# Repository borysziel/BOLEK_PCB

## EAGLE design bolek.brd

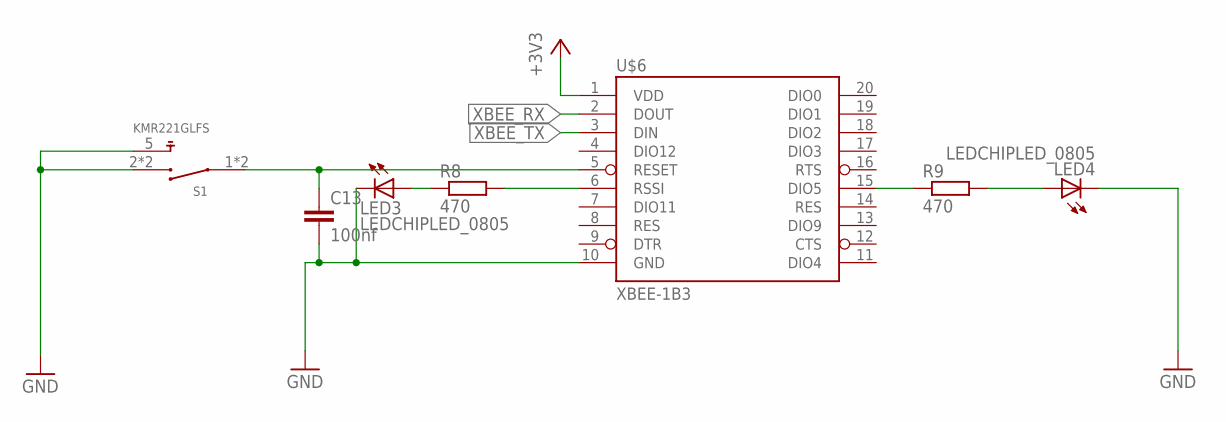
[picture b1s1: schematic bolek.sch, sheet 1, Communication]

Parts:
C13: 100nf; C0603
LED3, LED4: LEDCHIPLED_0805; CHIPLED_0805
R8, R9: 470; R0603
S1: KMR221GLFS; SW_KMR221GLFS
U$6: XBEE-1B3; XBEE-SMD

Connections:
+3V3: U$6.1 (VDD); also elsewhere on the board
GND: C13.2, LED3.C, LED4.C, S1.2 (3), S1.3, S1.5, U$6.10 (GND); also elsewhere on the board
unnamed: C13.1, S1.1, S1.4 (1), U$6.5 (RESET)
unnamed: R8.2, U$6.6 (RSSI)
unnamed: LED3.A, R8.1
unnamed: R9.1, U$6.15 (DIO5)
unnamed: LED4.A, R9.2
XBEE_RX: U$6.2 (DOUT); also elsewhere on the board
XBEE_TX: U$6.3 (DIN); also elsewhere on the board

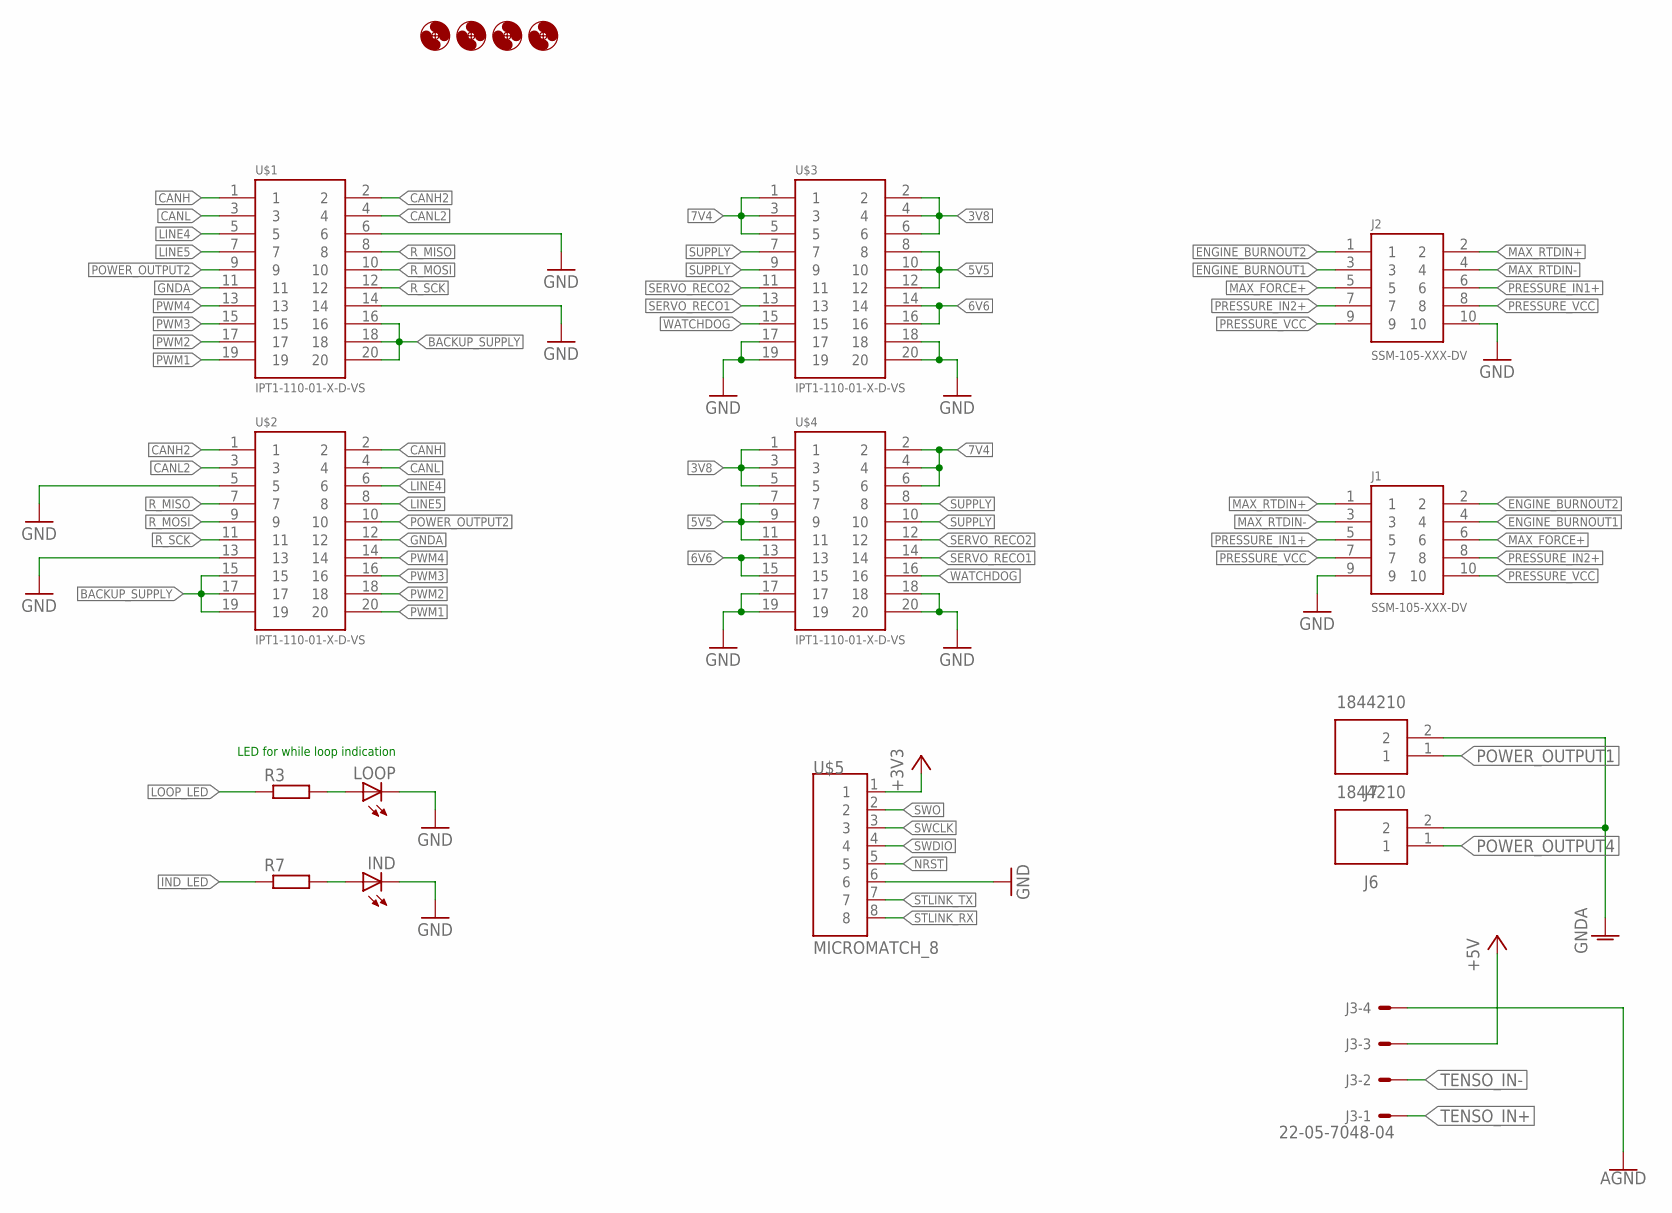
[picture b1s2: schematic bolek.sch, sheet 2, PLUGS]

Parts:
H1, H2, H3, H4: MOUNT-HOLE3.2; 3,2
IND: LEDCHIPLED_0603; CHIPLED_0603
J1, J2: SSM-105-XXX-DV
J3: 22-05-7048-04; 7395-04
J6, J7: 1844210; SHDR2W100P0X350_1X2_840X920X72
LOOP: LEDCHIPLED_0603; CHIPLED_0603
R3, R7: R-EU_R0603; R0603
U$1, U$2, U$3, U$4: IPT1-110-01-X-D-VS
U$5: MICROMATCH_8

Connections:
3V8: U$3.2, U$3.4, U$3.6, U$4.1, U$4.3, U$4.5; also elsewhere on the board
5V5: U$3.8, U$3.10, U$3.12, U$4.7, U$4.9, U$4.11; also elsewhere on the board
6V6: U$3.14, U$3.16, U$4.13, U$4.15
7V4: U$3.1, U$3.3, U$3.5, U$4.2, U$4.4, U$4.6
+3V3: U$5.1; also elsewhere on the board
+5V: J3.3; also elsewhere on the board
AGND: J3.4; also elsewhere on the board
BACKUP_SUPPLY: U$1.16, U$1.18, U$1.20, U$2.15, U$2.17, U$2.19
CANH: U$1.1, U$2.2; also elsewhere on the board
CANH2: U$1.2, U$2.1; also elsewhere on the board
CANL: U$1.3, U$2.4; also elsewhere on the board
CANL2: U$1.4, U$2.3; also elsewhere on the board
ENGINE_BURNOUT1: J1.4, J2.3; also elsewhere on the board
ENGINE_BURNOUT2: J1.2, J2.1; also elsewhere on the board
GND: IND.C, J1.9, J2.10, LOOP.C, U$1.6, U$1.14, U$2.5, U$2.13, U$3.17, U$3.18, U$3.19, U$3.20, U$4.17, U$4.18, U$4.19, U$4.20, U$5.6; also elsewhere on the board
GNDA: J6.2, J7.2, U$1.11, U$2.12; also elsewhere on the board
IND_LED: R7.1; also elsewhere on the board
LINE4: U$1.5, U$2.6
LINE5: U$1.7, U$2.8
LOOP_LED: R3.1; also elsewhere on the board
MAX_FORCE+: J1.6, J2.5; also elsewhere on the board
MAX_RTDIN+: J1.1, J2.2; also elsewhere on the board
MAX_RTDIN-: J1.3, J2.4; also elsewhere on the board
unnamed: LOOP.A, R3.2
unnamed: IND.A, R7.2
NRST: U$5.5; also elsewhere on the board
POWER_OUTPUT1: J7.1; also elsewhere on the board
POWER_OUTPUT2: U$1.9, U$2.10; also elsewhere on the board
POWER_OUTPUT4: J6.1; also elsewhere on the board
PRESSURE_IN1+: J1.5, J2.6; also elsewhere on the board
PRESSURE_IN2+: J1.8, J2.7; also elsewhere on the board
PRESSURE_VCC: J1.7, J1.10, J2.8, J2.9; also elsewhere on the board
PWM1: U$1.19, U$2.20; also elsewhere on the board
PWM2: U$1.17, U$2.18; also elsewhere on the board
PWM3: U$1.15, U$2.16
PWM4: U$1.13, U$2.14
R_MISO: U$1.8, U$2.7
R_MOSI: U$1.10, U$2.9
R_SCK: U$1.12, U$2.11
SERVO_RECO1: U$3.13, U$4.14
SERVO_RECO2: U$3.11, U$4.12
STLINK_RX: U$5.8; also elsewhere on the board
STLINK_TX: U$5.7; also elsewhere on the board
SUPPLY: U$3.7, U$3.9, U$4.8, U$4.10; also elsewhere on the board
SWCLK: U$5.3; also elsewhere on the board
SWDIO: U$5.4; also elsewhere on the board
SWO: U$5.2
TENSO_IN+: J3.1; also elsewhere on the board
TENSO_IN-: J3.2; also elsewhere on the board
WATCHDOG: U$3.15, U$4.16

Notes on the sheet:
LED for while loop indication

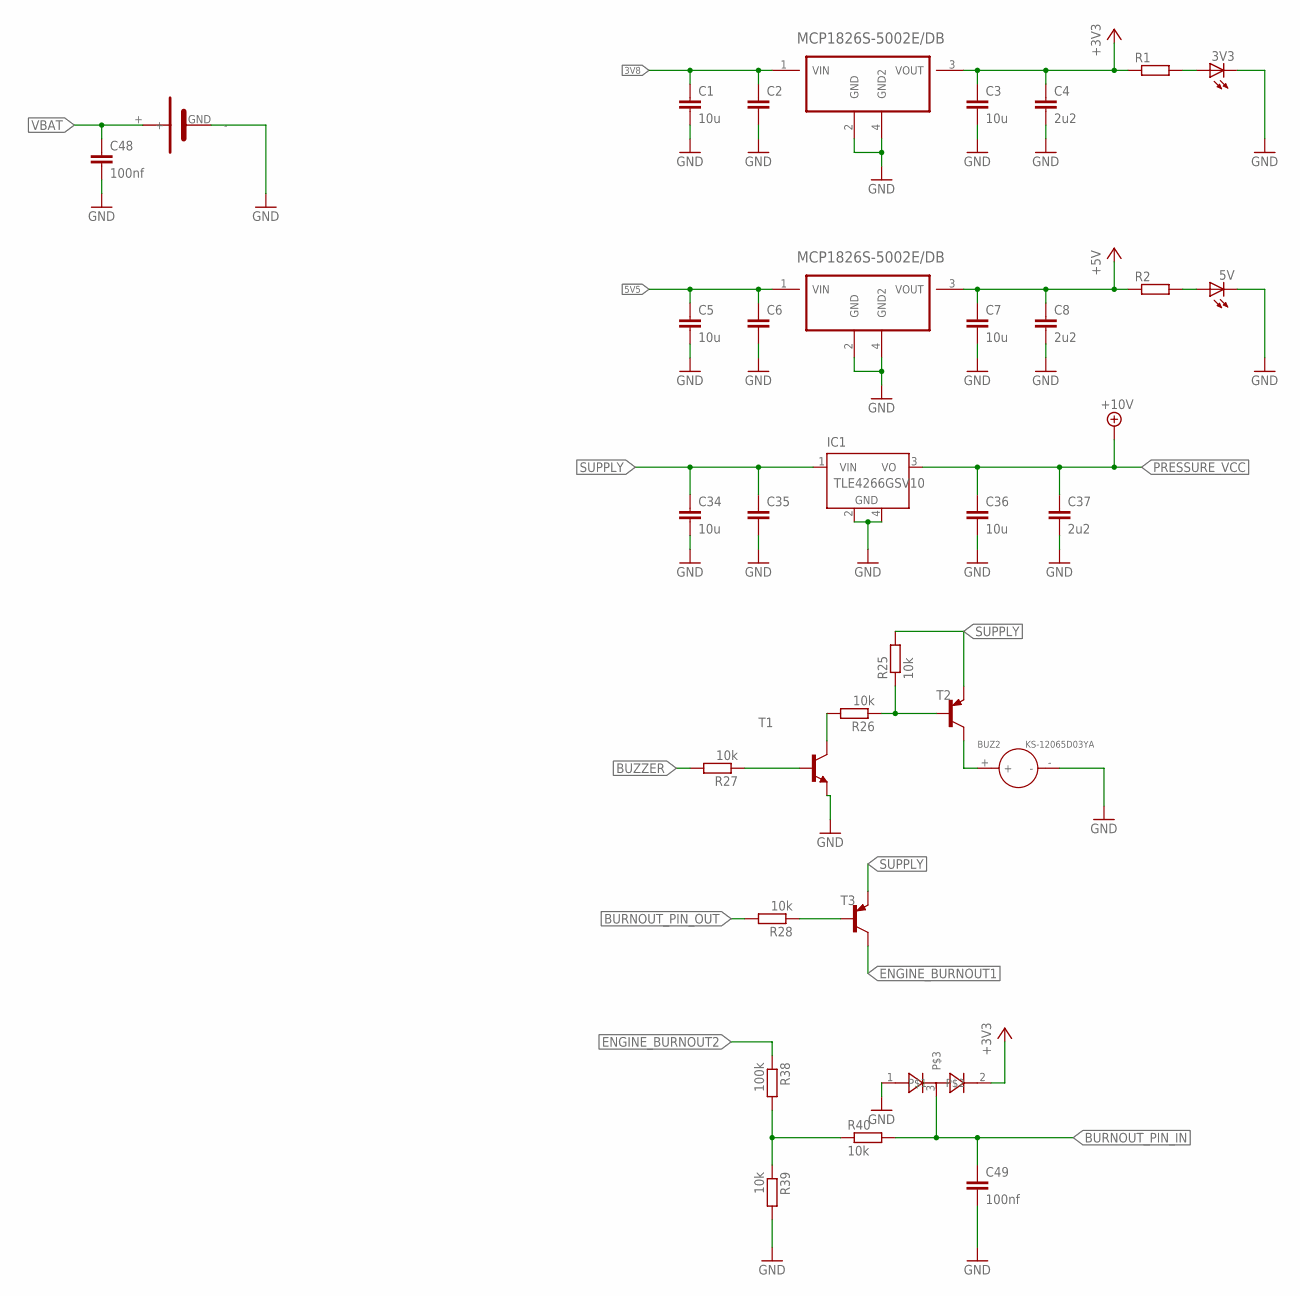
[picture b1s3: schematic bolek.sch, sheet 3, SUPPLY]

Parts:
3V3, 5V: LEDCHIPLED_0603; CHIPLED_0603
BUZ2: KS-12065D03YA; BZ2-7.6-D12.0XH6.5MM
C1, C3, C5, C7, C34, C36: 10u; C0805K
C2, C6, C35: C-EUC0805K; C0805K
C4, C8, C37: 2u2; C0805K
C48: 100nf; C0805K
C49: 100nf; C0603
IC1: TLE4266GSV10; SOT223
R1, R2: R-EU_R0603; R0603
R25, R26, R27, R28, R39, R40: 10k; R0603
R38: 100k; R0603
T1: BCW81-NPN-SOT23-BEC; SOT23-BEC
T2, T3: BC807-16-PNP-SOT23-BEC; SOT23-BEC
U1, U2: MCP1826S-5002E/DB; SOT230P700X180-4N
U$32: CR1220_POZ
U$40: BAS40W-04; SOT65P210X110-3N

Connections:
3V8: C1.1, C2.1, U1.1 (VIN); also elsewhere on the board
5V5: C5.1, C6.1, U2.1 (VIN); also elsewhere on the board
+3V3: C3.1, C4.1, R1.1, U1.3 (VOUT), U$40.2; also elsewhere on the board
+5V: C7.1, C8.1, R2.1, U2.3 (VOUT); also elsewhere on the board
BURNOUT_PIN_IN: C49.1, R40.2, U$40.3; also elsewhere on the board
BURNOUT_PIN_OUT: R28.2; also elsewhere on the board
BUZZER: R27.2; also elsewhere on the board
ENGINE_BURNOUT1: T3.C; also elsewhere on the board
ENGINE_BURNOUT2: R38.1; also elsewhere on the board
GND: 3V3.C, 5V.C, BUZ2.-, C1.2, C2.2, C3.2, C4.2, C5.2, C6.2, C7.2, C8.2, C34.2, C35.2, C36.2, C37.2, C48.2, C49.2, IC1.2 (GND), IC1.4 (GND), R39.2, T1.E, U1.2 (GND), U1.4 (GND2), U2.2 (GND), U2.4 (GND2), U$32.GND (-), U$40.1; also elsewhere on the board
unnamed: 3V3.A, R1.2
unnamed: 5V.A, R2.2
unnamed: R25.1, R26.1, T2.B
unnamed: BUZ2.+, T2.C
unnamed: R26.2, T1.C
unnamed: R27.1, T1.B
unnamed: R28.1, T3.B
unnamed: R38.2, R39.1, R40.1
PRESSURE_VCC: C36.1, C37.1, IC1.3 (VO); also elsewhere on the board
SUPPLY: C34.1, C35.1, IC1.1 (VIN), R25.2, T2.E, T3.E; also elsewhere on the board
VBAT: C48.1, U$32.+; also elsewhere on the board

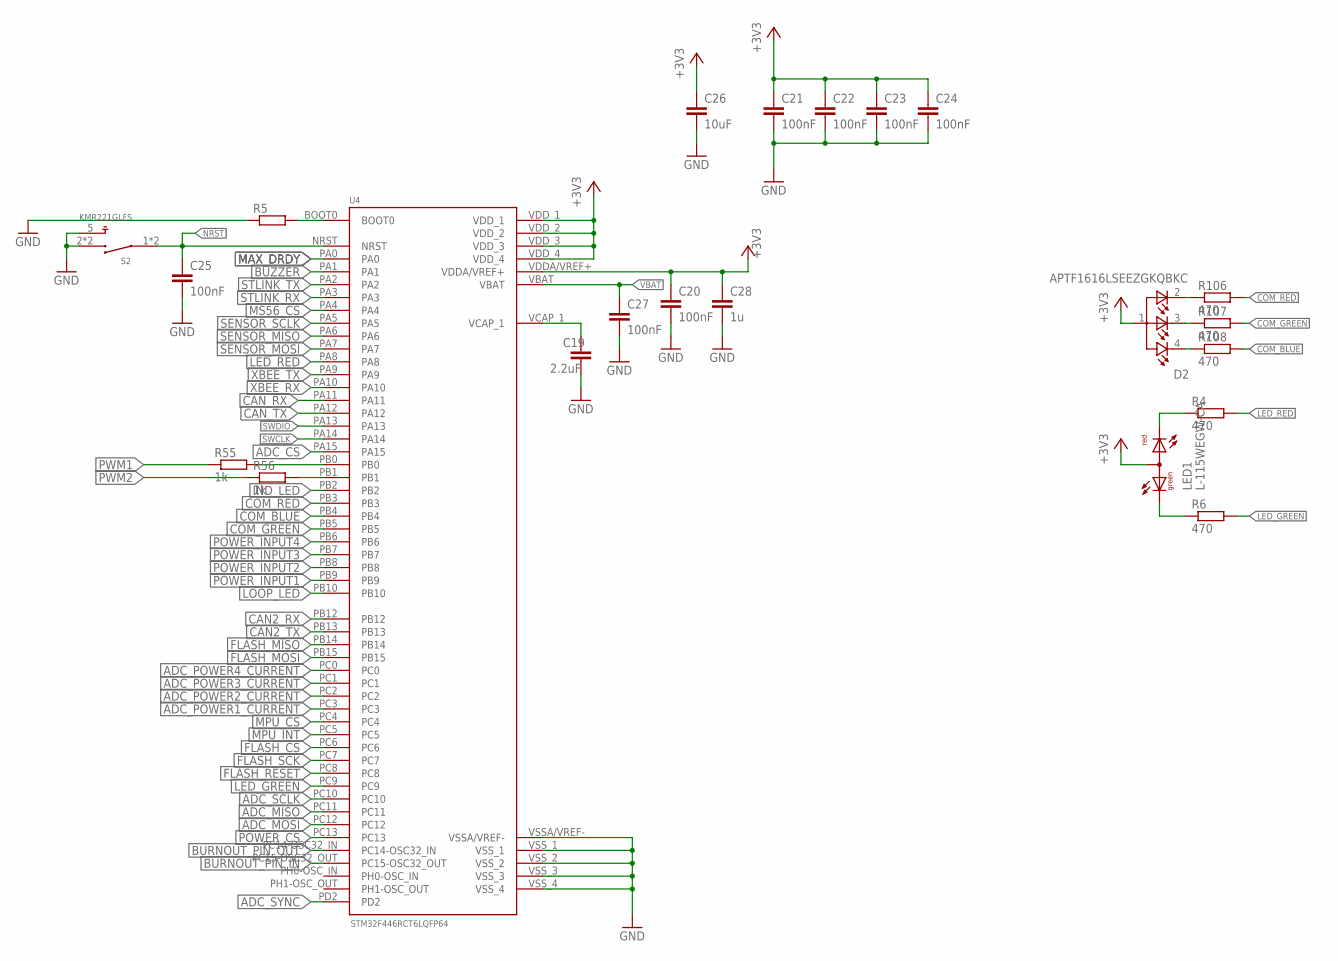
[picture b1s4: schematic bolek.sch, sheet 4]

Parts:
C19: 2.2uF; C0603K
C20, C21, C22, C23, C24, C25, C27: 100nF; C0603K
C26: 10uF; C0805K
C28: 1u; C0603K
D2: APTF1616LSEEZGKQBKC; LEDSC160X160X070-4N
LED1: L-115WEGW-CA; DUOLED-A-3MM
R4, R6, R106, R107, R108: 470; R0603
R5: R-EU_R0603; R0603
R55, R56: 1k; R0603
S2: KMR221GLFS; SW_KMR221GLFS
U4: STM32F446RCT6LQFP64; QFP50P1290X1290X120-64

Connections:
+3V3: C20.1, C21.1, C22.1, C23.1, C24.1, C26.1, C28.1, D2.1, LED1.2 (A), U4.VDDA/VREF+, U4.VDD_1, U4.VDD_2, U4.VDD_3, U4.VDD_4; also elsewhere on the board
ADC_CS: U4.PA15; also elsewhere on the board
ADC_MISO: U4.PC11; also elsewhere on the board
ADC_MOSI: U4.PC12; also elsewhere on the board
ADC_POWER1_CURRENT: U4.PC3; also elsewhere on the board
ADC_POWER2_CURRENT: U4.PC2; also elsewhere on the board
ADC_POWER3_CURRENT: U4.PC1; also elsewhere on the board
ADC_POWER4_CURRENT: U4.PC0; also elsewhere on the board
ADC_SCLK: U4.PC10; also elsewhere on the board
ADC_SYNC: U4.PD2; also elsewhere on the board
BURNOUT_PIN_IN: U4.PC15-OSC32_OUT; also elsewhere on the board
BURNOUT_PIN_OUT: U4.PC14-OSC32_IN; also elsewhere on the board
BUZZER: U4.PA1; also elsewhere on the board
CAN2_RX: U4.PB12; also elsewhere on the board
CAN2_TX: U4.PB13; also elsewhere on the board
CAN_RX: U4.PA11; also elsewhere on the board
CAN_TX: U4.PA12; also elsewhere on the board
COM_BLUE: R108.2, U4.PB4
COM_GREEN: R107.2, U4.PB5
COM_RED: R106.2, U4.PB3
FLASH_CS: U4.PC6; also elsewhere on the board
FLASH_MISO: U4.PB14; also elsewhere on the board
FLASH_MOSI: U4.PB15; also elsewhere on the board
FLASH_RESET: U4.PC8; also elsewhere on the board
FLASH_SCK: U4.PC7; also elsewhere on the board
GND: C19.2, C20.2, C21.2, C22.2, C23.2, C24.2, C25.2, C26.2, C27.2, C28.2, R5.1, S2.2 (3), S2.3, S2.5, U4.VSSA/VREF-, U4.VSS_1, U4.VSS_2, U4.VSS_3, U4.VSS_4; also elsewhere on the board
IND_LED: U4.PB2; also elsewhere on the board
LED_GREEN: R6.2, U4.PC9
LED_RED: R4.2, U4.PA8
LOOP_LED: U4.PB10; also elsewhere on the board
MAX_DRDY: U4.PA0; also elsewhere on the board
MPU_CS: U4.PC4; also elsewhere on the board
MPU_INT: U4.PC5; also elsewhere on the board
MS56_CS: U4.PA4; also elsewhere on the board
unnamed: LED1.3 (CR), R4.1
unnamed: R5.2, U4.BOOT0
unnamed: LED1.1 (CG), R6.1
unnamed: R55.2, U4.PB0
unnamed: R56.2, U4.PB1
unnamed: D2.2, R106.1
unnamed: D2.3, R107.1
unnamed: D2.4, R108.1
NRST: C25.1, S2.1, S2.4 (1), U4.NRST; also elsewhere on the board
POWER_CS: U4.PC13; also elsewhere on the board
POWER_INPUT1: U4.PB9; also elsewhere on the board
POWER_INPUT2: U4.PB8; also elsewhere on the board
POWER_INPUT3: U4.PB7; also elsewhere on the board
POWER_INPUT4: U4.PB6; also elsewhere on the board
PWM1: R55.1; also elsewhere on the board
PWM2: R56.1; also elsewhere on the board
SENSOR_MISO: U4.PA6; also elsewhere on the board
SENSOR_MOSI: U4.PA7; also elsewhere on the board
SENSOR_SCLK: U4.PA5; also elsewhere on the board
STLINK_RX: U4.PA3; also elsewhere on the board
STLINK_TX: U4.PA2; also elsewhere on the board
SWCLK: U4.PA14; also elsewhere on the board
SWDIO: U4.PA13; also elsewhere on the board
VBAT: C27.1, U4.VBAT; also elsewhere on the board
VCAP1: C19.1, U4.VCAP_1
XBEE_RX: U4.PA10; also elsewhere on the board
XBEE_TX: U4.PA9; also elsewhere on the board

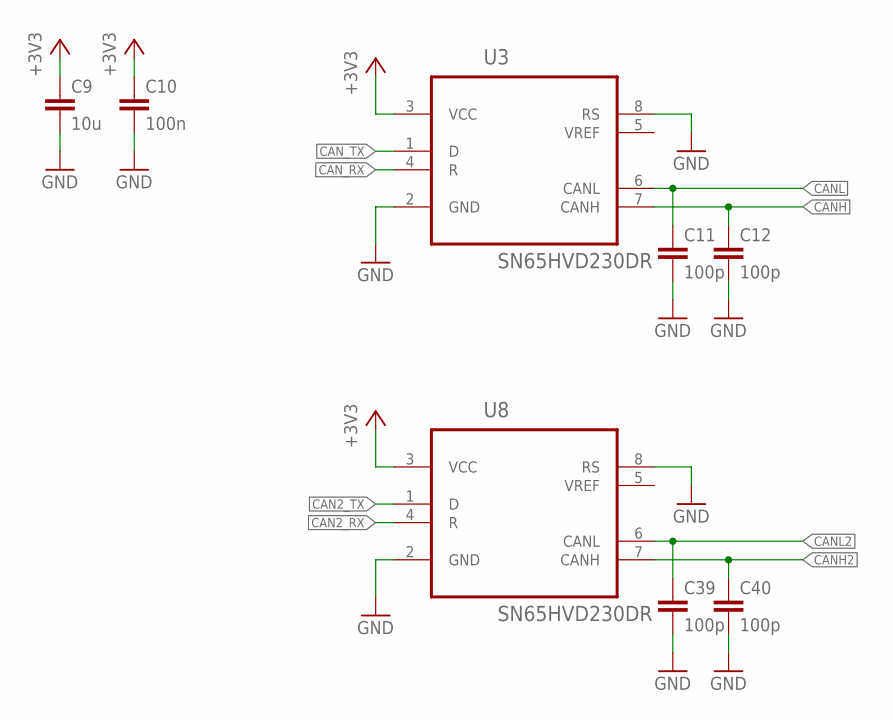
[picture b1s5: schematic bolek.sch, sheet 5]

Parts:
C9: 10u; C0805K
C10: 100n; C0603K
C11, C12, C39, C40: 100p; C0603K
U3, U8: SN65HVD230DR; SOIC127P600X175-8N

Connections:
+3V3: C9.1, C10.1, U3.3 (VCC), U8.3 (VCC); also elsewhere on the board
CAN2_RX: U8.4 (R); also elsewhere on the board
CAN2_TX: U8.1 (D); also elsewhere on the board
CANH: C12.1, U3.7 (CANH); also elsewhere on the board
CANH2: C40.1, U8.7 (CANH); also elsewhere on the board
CANL: C11.1, U3.6 (CANL); also elsewhere on the board
CANL2: C39.1, U8.6 (CANL); also elsewhere on the board
CAN_RX: U3.4 (R); also elsewhere on the board
CAN_TX: U3.1 (D); also elsewhere on the board
GND: C9.2, C10.2, C11.2, C12.2, C39.2, C40.2, U3.2 (GND), U3.8 (RS), U8.2 (GND), U8.8 (RS); also elsewhere on the board

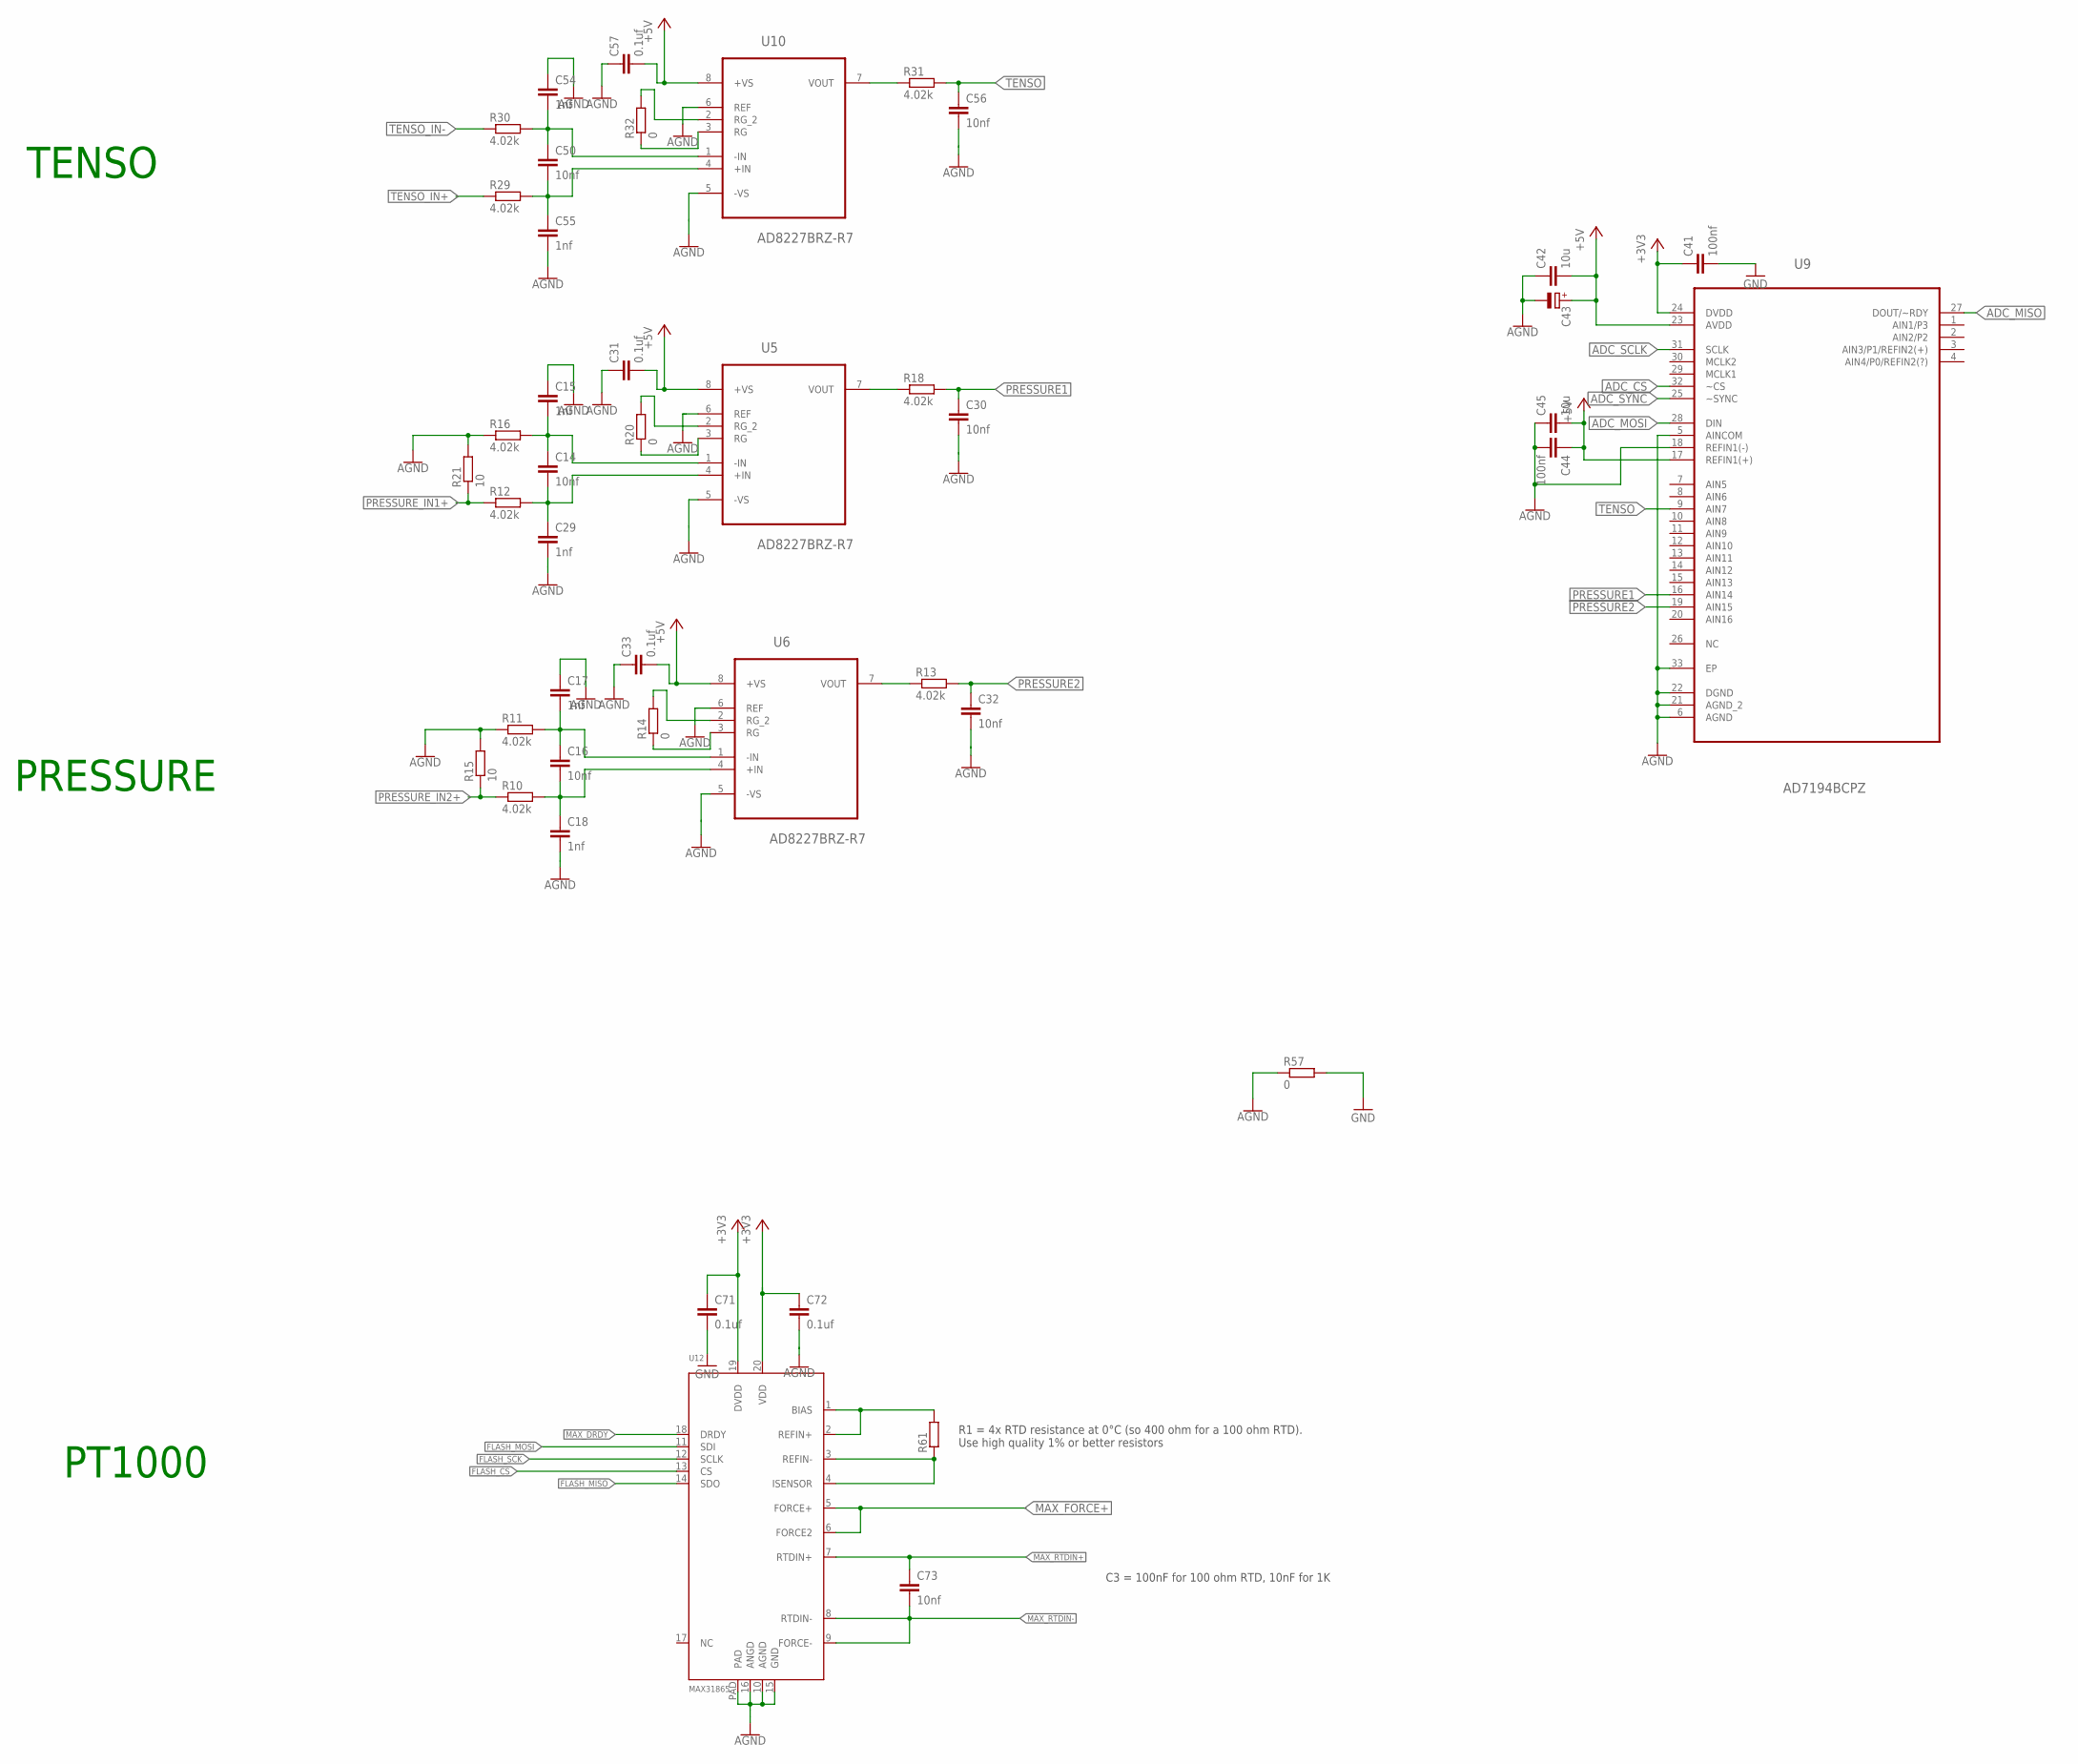
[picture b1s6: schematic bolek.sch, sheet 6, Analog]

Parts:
C14, C16, C30, C32, C50, C56, C73: 10nf; C0603
C15, C17, C18, C29, C54, C55: 1nf; C0603
C31, C33, C57, C71, C72: 0.1uf; C0603
C41, C44: 100nf; C0603K
C42, C45: 10u; C0805K
C43: CPOL-EUSMCA; SMC_A
R10, R11, R12, R13, R16, R18, R29, R30, R31: 4.02k; R0603
R14, R20, R32: 0; R0805
R15, R21: 10; R0603
R57: 0; R0603
R61: R-EU_R0805; R0805
U5, U6, U10: AD8227BRZ-R7; SOIC127P600X175-8N
U9: AD7194BCPZ; QFN50P500X500X80-33N
U12: MAX31865; QFN20_4MM_0.65MM

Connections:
+3V3: C41.1, C71.1, C72.1, U9.24 (DVDD), U12.19 (DVDD), U12.20 (VDD); also elsewhere on the board
+5V: C31.2, C33.2, C42.2, C43.+, C44.1, C45.2, C57.2, U5.8 (+VS), U6.8 (+VS), U9.17 (REFIN1(+)), U9.23 (AVDD), U10.8 (+VS); also elsewhere on the board
ADC_CS: U9.32 (~CS); also elsewhere on the board
ADC_MISO: U9.27 (DOUT/~RDY); also elsewhere on the board
ADC_MOSI: U9.28 (DIN); also elsewhere on the board
ADC_SCLK: U9.31 (SCLK); also elsewhere on the board
ADC_SYNC: U9.25 (~SYNC); also elsewhere on the board
AGND: C15.1, C17.1, C18.2, C29.2, C30.2, C31.1, C32.2, C33.1, C42.1, C43.-, C44.2, C45.1, C54.1, C55.2, C56.2, C57.1, C72.2, R11.1, R15.2, R16.1, R21.2, R57.1, U5.5 (-VS), U5.6 (REF), U6.5 (-VS), U6.6 (REF), U9.5 (AINCOM), U9.6 (AGND), U9.18 (REFIN1(-)), U9.21 (AGND_2), U9.22 (DGND), U9.33 (EP), U10.5 (-VS), U10.6 (REF), U12.10 (AGND), U12.15 (GND), U12.16 (ANGD), U12.PAD; also elsewhere on the board
FLASH_CS: U12.13 (CS); also elsewhere on the board
FLASH_MISO: U12.14 (SDO); also elsewhere on the board
FLASH_MOSI: U12.11 (SDI); also elsewhere on the board
FLASH_SCK: U12.12 (SCLK); also elsewhere on the board
GND: C41.2, C71.2, R57.2; also elsewhere on the board
MAX_DRDY: U12.18 (DRDY); also elsewhere on the board
MAX_FORCE+: U12.5 (FORCE+), U12.6 (FORCE2); also elsewhere on the board
MAX_RTDIN+: C73.1, U12.7 (RTDIN+); also elsewhere on the board
MAX_RTDIN-: C73.2, U12.8 (RTDIN-), U12.9 (FORCE-); also elsewhere on the board
unnamed: C16.1, C17.2, R11.2, U6.1 (-IN)
unnamed: C16.2, C18.1, R10.2, U6.4 (+IN)
unnamed: R13.1, U6.7 (VOUT)
unnamed: R14.1, U6.3 (RG)
unnamed: R14.2, U6.2 (RG_2)
unnamed: R61.2, U12.1 (BIAS), U12.2 (REFIN+)
unnamed: R61.1, U12.3 (REFIN-), U12.4 (ISENSOR)
unnamed: C14.1, C15.2, R16.2, U5.1 (-IN)
unnamed: C14.2, C29.1, R12.2, U5.4 (+IN)
unnamed: R18.1, U5.7 (VOUT)
unnamed: R20.1, U5.3 (RG)
unnamed: R20.2, U5.2 (RG_2)
unnamed: C50.1, C54.2, R30.2, U10.1 (-IN)
unnamed: C50.2, C55.1, R29.2, U10.4 (+IN)
unnamed: R31.1, U10.7 (VOUT)
unnamed: R32.1, U10.3 (RG)
unnamed: R32.2, U10.2 (RG_2)
PRESSURE1: C30.1, R18.2, U9.16 (AIN14)
PRESSURE2: C32.1, R13.2, U9.19 (AIN15)
PRESSURE_IN1+: R12.1, R21.1; also elsewhere on the board
PRESSURE_IN2+: R10.1, R15.1; also elsewhere on the board
TENSO: C56.1, R31.2, U9.9 (AIN7)
TENSO_IN+: R29.1; also elsewhere on the board
TENSO_IN-: R30.1; also elsewhere on the board

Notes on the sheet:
PRESSURE
TENSO
C3 = 100nF for 100 ohm RTD, 10nF for 1K
R1 = 4x RTD resistance at 0°C (so 400 ohm for a 100 ohm RTD). Use high quality 1% or better resistors
PT1000

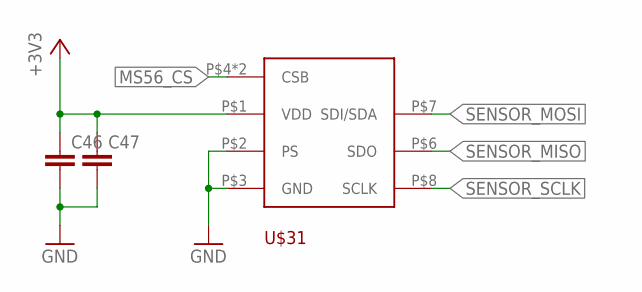
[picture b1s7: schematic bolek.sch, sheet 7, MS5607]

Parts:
C46, C47: C-EUC0603; C0603
U$31: MS56XX

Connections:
+3V3: C46.1, C47.1, U$31.P$1 (VDD); also elsewhere on the board
GND: C46.2, C47.2, U$31.P$2 (PS), U$31.P$3 (GND); also elsewhere on the board
MS56_CS: U$31.P$4 (CSB), U$31.P$5 (CSB); also elsewhere on the board
SENSOR_MISO: U$31.P$6 (SDO); also elsewhere on the board
SENSOR_MOSI: U$31.P$7 (SDI/SDA); also elsewhere on the board
SENSOR_SCLK: U$31.P$8 (SCLK); also elsewhere on the board

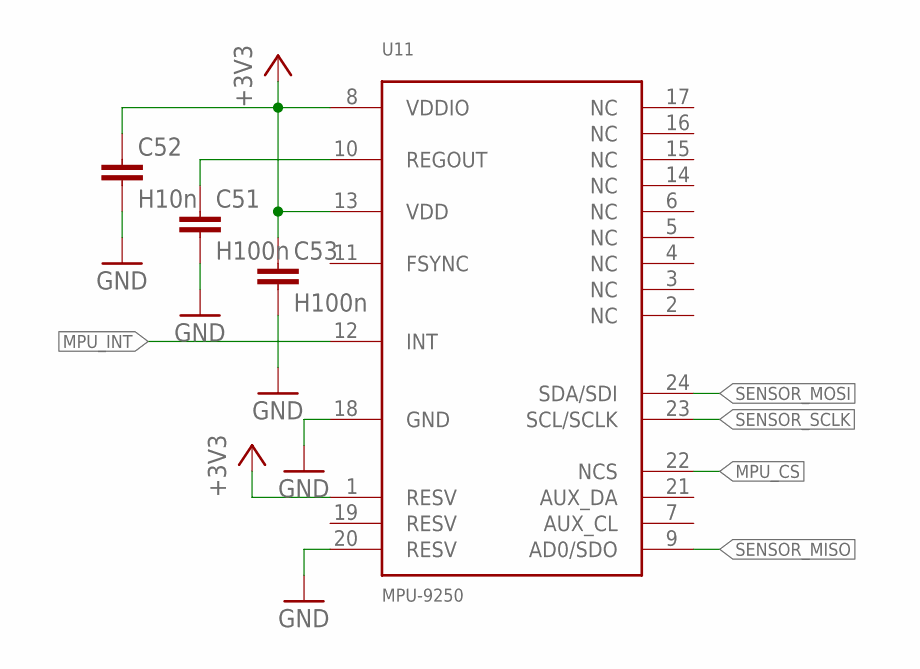
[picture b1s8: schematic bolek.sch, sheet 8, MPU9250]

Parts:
C51, C53: H100n; C0603K
C52: H10n; C0603K
U11: MPU-9250

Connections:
+3V3: C52.1, C53.1, U11.1 (RESV), U11.8 (VDDIO), U11.13 (VDD); also elsewhere on the board
GND: C51.2, C52.2, C53.2, U11.18 (GND), U11.20 (RESV); also elsewhere on the board
MPU_CS: U11.22 (NCS); also elsewhere on the board
MPU_INT: U11.12 (INT); also elsewhere on the board
unnamed: C51.1, U11.10 (REGOUT)
SENSOR_MISO: U11.9 (AD0/SDO); also elsewhere on the board
SENSOR_MOSI: U11.24 (SDA/SDI); also elsewhere on the board
SENSOR_SCLK: U11.23 (SCL/SCLK); also elsewhere on the board

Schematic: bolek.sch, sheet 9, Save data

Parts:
C58: 100nf; C0603
R33, R34, R35, R36, R37: 10; R0603
U$39: S25FLX; SOIC16

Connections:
+3V3: C58.1, U$39.2 (VCC); also elsewhere on the board
FLASH_CS: R36.2; also elsewhere on the board
FLASH_MISO: R35.2; also elsewhere on the board
FLASH_MOSI: R34.2; also elsewhere on the board
FLASH_RESET: R37.1; also elsewhere on the board
FLASH_SCK: R33.2; also elsewhere on the board
GND: C58.2, U$39.10 (VSS); also elsewhere on the board
unnamed: R33.1, U$39.16 (SCK)
unnamed: R34.1, U$39.15 (SI)
unnamed: R35.1, U$39.8 (SO)
unnamed: R36.1, U$39.7 (!CS)
unnamed: R37.2, U$39.3 (!RESET)

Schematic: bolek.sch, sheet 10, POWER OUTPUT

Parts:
C59, C60: 100nf; C0603
C61, C62, C63, C64, C65, C66, C67, C68: 10nf; C0603
D1: DIODE-SOD123; SOD123
R41, R42, R43, R44, R45, R46, R47, R48, R49: 10k; R0603
R50, R51, R52, R53, R54: 1k; R0603
R58: 0; R0603
VNQ5027AK-E1: VNQ5027AK-E; POWERSSO-24

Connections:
ADC_POWER1_CURRENT: C65.1, R46.2, R50.1; also elsewhere on the board
ADC_POWER2_CURRENT: C66.1, R47.2, R51.1; also elsewhere on the board
ADC_POWER3_CURRENT: C67.1, R48.2, R52.1; also elsewhere on the board
ADC_POWER4_CURRENT: C68.1, R49.2, R53.1; also elsewhere on the board
AGND: R58.2; also elsewhere on the board
GNDA: C59.2, C60.2, C61.2, C62.2, C63.2, C64.2, C65.2, C66.2, C67.2, C68.2, D1.C, R50.2, R51.2, R52.2, R53.2, R54.1, R58.1; also elsewhere on the board
unnamed: R46.1, VNQ5027AK-E1.P$4 (CURRENT_SENSE1)
unnamed: R47.1, VNQ5027AK-E1.P$6 (CURRENT_SENSE2)
unnamed: R48.1, VNQ5027AK-E1.P$8 (CURRENT_SENSE3)
unnamed: R49.1, VNQ5027AK-E1.P$10 (CURRENT_SENSE4)
unnamed: R41.2, VNQ5027AK-E1.P$3 (INPUT1)
unnamed: R42.2, VNQ5027AK-E1.P$5 (INPUT2)
unnamed: R43.2, VNQ5027AK-E1.P$7 (INPUT3)
unnamed: R44.2, VNQ5027AK-E1.P$9 (INPUT4)
unnamed: R45.2, VNQ5027AK-E1.P$11 (CS_DIS)
unnamed: D1.A, R54.2, VNQ5027AK-E1.P$2 (GND)
POWER_CS: R45.1; also elsewhere on the board
POWER_INPUT1: R41.1; also elsewhere on the board
POWER_INPUT2: R42.1; also elsewhere on the board
POWER_INPUT3: R43.1; also elsewhere on the board
POWER_INPUT4: R44.1; also elsewhere on the board
POWER_OUTPUT1: C61.1, VNQ5027AK-E1.P$13 (OUTPUT1_1), VNQ5027AK-E1.P$14 (OUTPUT1_2), VNQ5027AK-E1.P$15 (OUTPUT1_3); also elsewhere on the board
POWER_OUTPUT2: C62.1, VNQ5027AK-E1.P$16 (OUTPUT2_1), VNQ5027AK-E1.P$17 (OUTPUT2_2), VNQ5027AK-E1.P$18 (OUTPUT2_3); also elsewhere on the board
POWER_OUTPUT3: C63.1, VNQ5027AK-E1.P$19 (OUTPUT3_1), VNQ5027AK-E1.P$20 (OUTPUT3_2), VNQ5027AK-E1.P$21 (OUTPUT3_3)
POWER_OUTPUT4: C64.1, VNQ5027AK-E1.P$22 (OUTPUT4_1), VNQ5027AK-E1.P$23 (OUTPUT4_2), VNQ5027AK-E1.P$24 (OUTPUT4_3); also elsewhere on the board
SUPPLY: C59.1, C60.1, VNQ5027AK-E1.P$1 (VCC), VNQ5027AK-E1.P$12 (VCC_1), VNQ5027AK-E1.P$25 (VCC_PAD); also elsewhere on the board

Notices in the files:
parts and their libraries:
SparkFun: Licensing: CC v3.0 Share-Alike You are welcome to use this library for commercial purposes.
microbuilder: This work is placed in the public domain, and may be freely used for commercial and non-commercial work with the following conditions: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
